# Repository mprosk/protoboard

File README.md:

# protoboard
General purpose prototyping breadboard

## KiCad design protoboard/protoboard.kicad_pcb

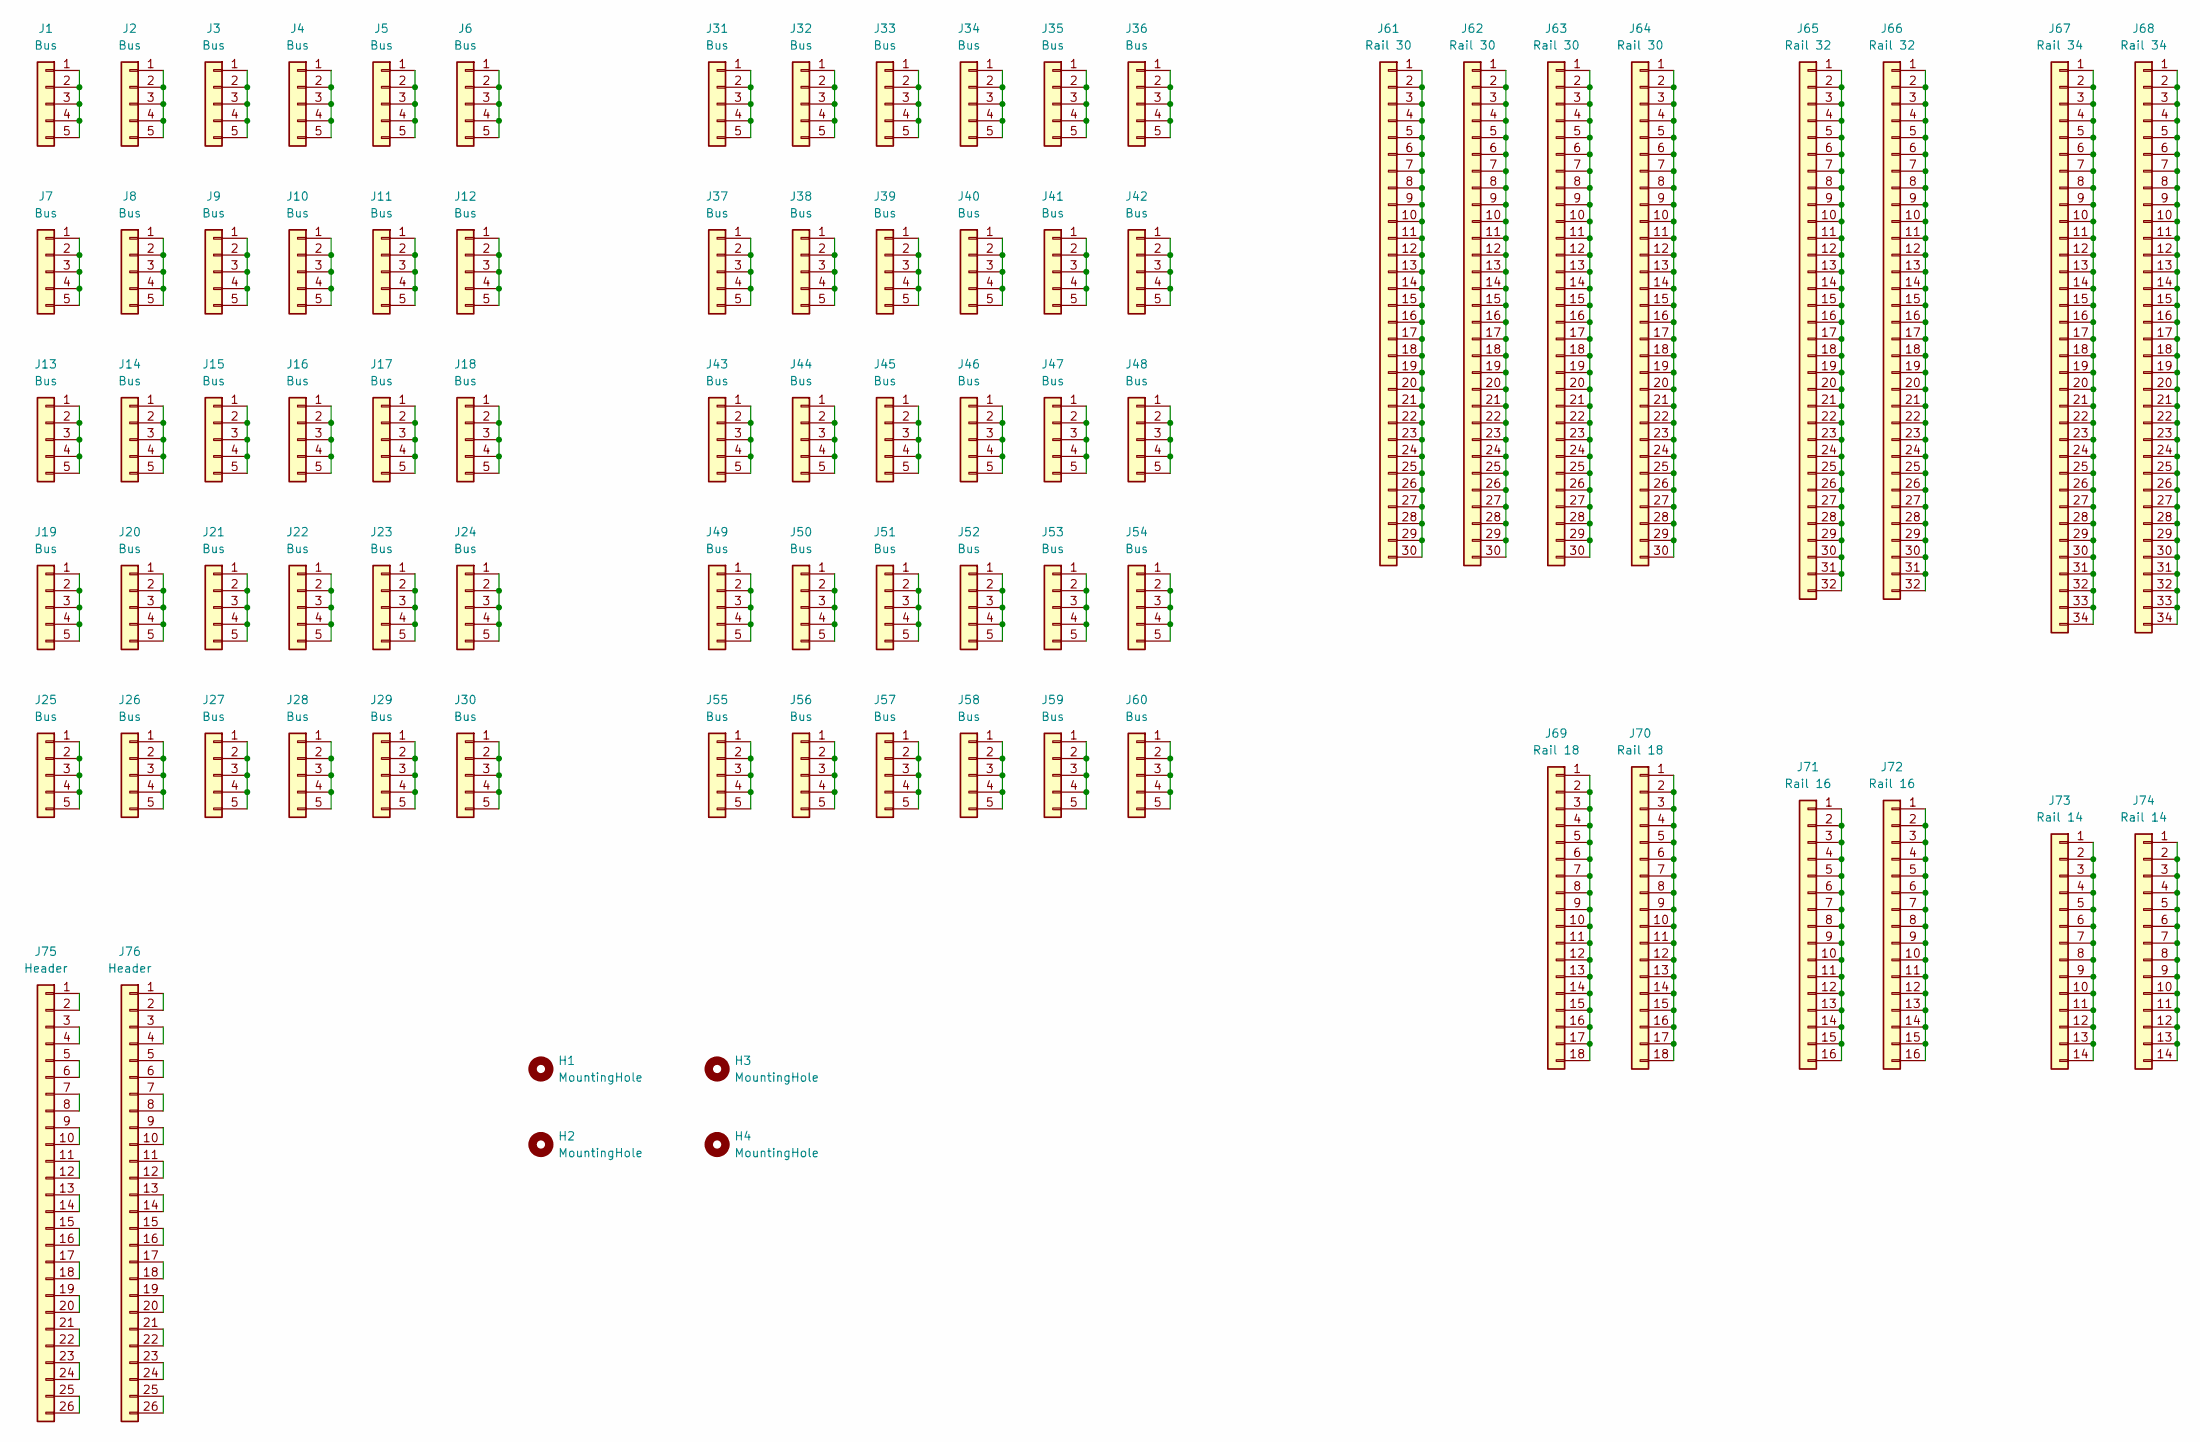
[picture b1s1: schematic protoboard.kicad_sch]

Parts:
H1, H2, H3, H4: MountingHole; MountingHole_3.2mm_M3
J1, J2, J3, J4, J5, J6, J7, J8, J9, J10, J11, J12, J13, J14, J15, J16, J17, J18, J19, J20, J21, J22, J23, J24, J25, J26, J27, J28, J29, J30, J31, J32, J33, J34, J35, J36, J37, J38, J39, J40, J41, J42, J43, J44, J45, J46, J47, J48, J49, J50, J51, J52, J53, J54, J55, J56, J57, J58, J59, J60: Bus
J61, J62, J63, J64: Rail 30; Rail_30
J65, J66: Rail 32; Rail_32
J67, J68: Rail 34; Rail_34
J69, J70: Rail 18; Rail_18
J71, J72: Rail 16; Rail_16
J73, J74: Rail 14; Rail_14
J75, J76: Header

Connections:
unnamed: J1.1, J1.2, J1.3, J1.4, J1.5
unnamed: J2.1, J2.2, J2.3, J2.4, J2.5
unnamed: J3.1, J3.2, J3.3, J3.4, J3.5
unnamed: J4.1, J4.2, J4.3, J4.4, J4.5
unnamed: J5.1, J5.2, J5.3, J5.4, J5.5
unnamed: J6.1, J6.2, J6.3, J6.4, J6.5
unnamed: J7.1, J7.2, J7.3, J7.4, J7.5
unnamed: J8.1, J8.2, J8.3, J8.4, J8.5
unnamed: J9.1, J9.2, J9.3, J9.4, J9.5
unnamed: J10.1, J10.2, J10.3, J10.4, J10.5
unnamed: J11.1, J11.2, J11.3, J11.4, J11.5
unnamed: J12.1, J12.2, J12.3, J12.4, J12.5
unnamed: J13.1, J13.2, J13.3, J13.4, J13.5
unnamed: J14.1, J14.2, J14.3, J14.4, J14.5
unnamed: J15.1, J15.2, J15.3, J15.4, J15.5
unnamed: J16.1, J16.2, J16.3, J16.4, J16.5
unnamed: J17.1, J17.2, J17.3, J17.4, J17.5
unnamed: J18.1, J18.2, J18.3, J18.4, J18.5
unnamed: J19.1, J19.2, J19.3, J19.4, J19.5
unnamed: J20.1, J20.2, J20.3, J20.4, J20.5
unnamed: J21.1, J21.2, J21.3, J21.4, J21.5
unnamed: J22.1, J22.2, J22.3, J22.4, J22.5
unnamed: J23.1, J23.2, J23.3, J23.4, J23.5
unnamed: J24.1, J24.2, J24.3, J24.4, J24.5
unnamed: J25.1, J25.2, J25.3, J25.4, J25.5
unnamed: J26.1, J26.2, J26.3, J26.4, J26.5
unnamed: J27.1, J27.2, J27.3, J27.4, J27.5
unnamed: J28.1, J28.2, J28.3, J28.4, J28.5
unnamed: J29.1, J29.2, J29.3, J29.4, J29.5
unnamed: J30.1, J30.2, J30.3, J30.4, J30.5
unnamed: J31.1, J31.2, J31.3, J31.4, J31.5
unnamed: J32.1, J32.2, J32.3, J32.4, J32.5
unnamed: J33.1, J33.2, J33.3, J33.4, J33.5
unnamed: J34.1, J34.2, J34.3, J34.4, J34.5
unnamed: J35.1, J35.2, J35.3, J35.4, J35.5
unnamed: J36.1, J36.2, J36.3, J36.4, J36.5
unnamed: J37.1, J37.2, J37.3, J37.4, J37.5
unnamed: J38.1, J38.2, J38.3, J38.4, J38.5
unnamed: J39.1, J39.2, J39.3, J39.4, J39.5
unnamed: J40.1, J40.2, J40.3, J40.4, J40.5
unnamed: J41.1, J41.2, J41.3, J41.4, J41.5
unnamed: J42.1, J42.2, J42.3, J42.4, J42.5
unnamed: J43.1, J43.2, J43.3, J43.4, J43.5
unnamed: J44.1, J44.2, J44.3, J44.4, J44.5
unnamed: J45.1, J45.2, J45.3, J45.4, J45.5
unnamed: J46.1, J46.2, J46.3, J46.4, J46.5
unnamed: J47.1, J47.2, J47.3, J47.4, J47.5
unnamed: J48.1, J48.2, J48.3, J48.4, J48.5
unnamed: J49.1, J49.2, J49.3, J49.4, J49.5
unnamed: J50.1, J50.2, J50.3, J50.4, J50.5
unnamed: J51.1, J51.2, J51.3, J51.4, J51.5
unnamed: J52.1, J52.2, J52.3, J52.4, J52.5
unnamed: J53.1, J53.2, J53.3, J53.4, J53.5
unnamed: J54.1, J54.2, J54.3, J54.4, J54.5
unnamed: J55.1, J55.2, J55.3, J55.4, J55.5
unnamed: J56.1, J56.2, J56.3, J56.4, J56.5
unnamed: J57.1, J57.2, J57.3, J57.4, J57.5
unnamed: J58.1, J58.2, J58.3, J58.4, J58.5
unnamed: J59.1, J59.2, J59.3, J59.4, J59.5
unnamed: J60.1, J60.2, J60.3, J60.4, J60.5
unnamed: J61.1, J61.2, J61.3, J61.4, J61.5, J61.6, J61.7, J61.8, J61.9, J61.10, J61.11, J61.12, J61.13, J61.14, J61.15, J61.16, J61.17, J61.18, J61.19, J61.20, J61.21, J61.22, J61.23, J61.24, J61.25, J61.26, J61.27, J61.28, J61.29, J61.30
unnamed: J62.1, J62.2, J62.3, J62.4, J62.5, J62.6, J62.7, J62.8, J62.9, J62.10, J62.11, J62.12, J62.13, J62.14, J62.15, J62.16, J62.17, J62.18, J62.19, J62.20, J62.21, J62.22, J62.23, J62.24, J62.25, J62.26, J62.27, J62.28, J62.29, J62.30
unnamed: J63.1, J63.2, J63.3, J63.4, J63.5, J63.6, J63.7, J63.8, J63.9, J63.10, J63.11, J63.12, J63.13, J63.14, J63.15, J63.16, J63.17, J63.18, J63.19, J63.20, J63.21, J63.22, J63.23, J63.24, J63.25, J63.26, J63.27, J63.28, J63.29, J63.30
unnamed: J64.1, J64.2, J64.3, J64.4, J64.5, J64.6, J64.7, J64.8, J64.9, J64.10, J64.11, J64.12, J64.13, J64.14, J64.15, J64.16, J64.17, J64.18, J64.19, J64.20, J64.21, J64.22, J64.23, J64.24, J64.25, J64.26, J64.27, J64.28, J64.29, J64.30
unnamed: J65.1, J65.2, J65.3, J65.4, J65.5, J65.6, J65.7, J65.8, J65.9, J65.10, J65.11, J65.12, J65.13, J65.14, J65.15, J65.16, J65.17, J65.18, J65.19, J65.20, J65.21, J65.22, J65.23, J65.24, J65.25, J65.26, J65.27, J65.28, J65.29, J65.30, J65.31, J65.32
unnamed: J66.1, J66.2, J66.3, J66.4, J66.5, J66.6, J66.7, J66.8, J66.9, J66.10, J66.11, J66.12, J66.13, J66.14, J66.15, J66.16, J66.17, J66.18, J66.19, J66.20, J66.21, J66.22, J66.23, J66.24, J66.25, J66.26, J66.27, J66.28, J66.29, J66.30, J66.31, J66.32
unnamed: J67.1, J67.2, J67.3, J67.4, J67.5, J67.6, J67.7, J67.8, J67.9, J67.10, J67.11, J67.12, J67.13, J67.14, J67.15, J67.16, J67.17, J67.18, J67.19, J67.20, J67.21, J67.22, J67.23, J67.24, J67.25, J67.26, J67.27, J67.28, J67.29, J67.30, J67.31, J67.32, J67.33, J67.34
unnamed: J68.1, J68.2, J68.3, J68.4, J68.5, J68.6, J68.7, J68.8, J68.9, J68.10, J68.11, J68.12, J68.13, J68.14, J68.15, J68.16, J68.17, J68.18, J68.19, J68.20, J68.21, J68.22, J68.23, J68.24, J68.25, J68.26, J68.27, J68.28, J68.29, J68.30, J68.31, J68.32, J68.33, J68.34
unnamed: J69.1, J69.2, J69.3, J69.4, J69.5, J69.6, J69.7, J69.8, J69.9, J69.10, J69.11, J69.12, J69.13, J69.14, J69.15, J69.16, J69.17, J69.18
unnamed: J70.1, J70.2, J70.3, J70.4, J70.5, J70.6, J70.7, J70.8, J70.9, J70.10, J70.11, J70.12, J70.13, J70.14, J70.15, J70.16, J70.17, J70.18
unnamed: J71.1, J71.2, J71.3, J71.4, J71.5, J71.6, J71.7, J71.8, J71.9, J71.10, J71.11, J71.12, J71.13, J71.14, J71.15, J71.16
unnamed: J72.1, J72.2, J72.3, J72.4, J72.5, J72.6, J72.7, J72.8, J72.9, J72.10, J72.11, J72.12, J72.13, J72.14, J72.15, J72.16
unnamed: J73.1, J73.2, J73.3, J73.4, J73.5, J73.6, J73.7, J73.8, J73.9, J73.10, J73.11, J73.12, J73.13, J73.14
unnamed: J74.1, J74.2, J74.3, J74.4, J74.5, J74.6, J74.7, J74.8, J74.9, J74.10, J74.11, J74.12, J74.13, J74.14
unnamed: J75.1, J75.2
unnamed: J75.3, J75.4
unnamed: J75.5, J75.6
unnamed: J75.7, J75.8
unnamed: J75.9, J75.10
unnamed: J75.11, J75.12
unnamed: J75.13, J75.14
unnamed: J75.15, J75.16
unnamed: J75.17, J75.18
unnamed: J75.19, J75.20
unnamed: J75.21, J75.22
unnamed: J75.23, J75.24
unnamed: J75.25, J75.26
unnamed: J76.1, J76.2
unnamed: J76.3, J76.4
unnamed: J76.5, J76.6
unnamed: J76.7, J76.8
unnamed: J76.9, J76.10
unnamed: J76.11, J76.12
unnamed: J76.13, J76.14
unnamed: J76.15, J76.16
unnamed: J76.17, J76.18
unnamed: J76.19, J76.20
unnamed: J76.21, J76.22
unnamed: J76.23, J76.24
unnamed: J76.25, J76.26

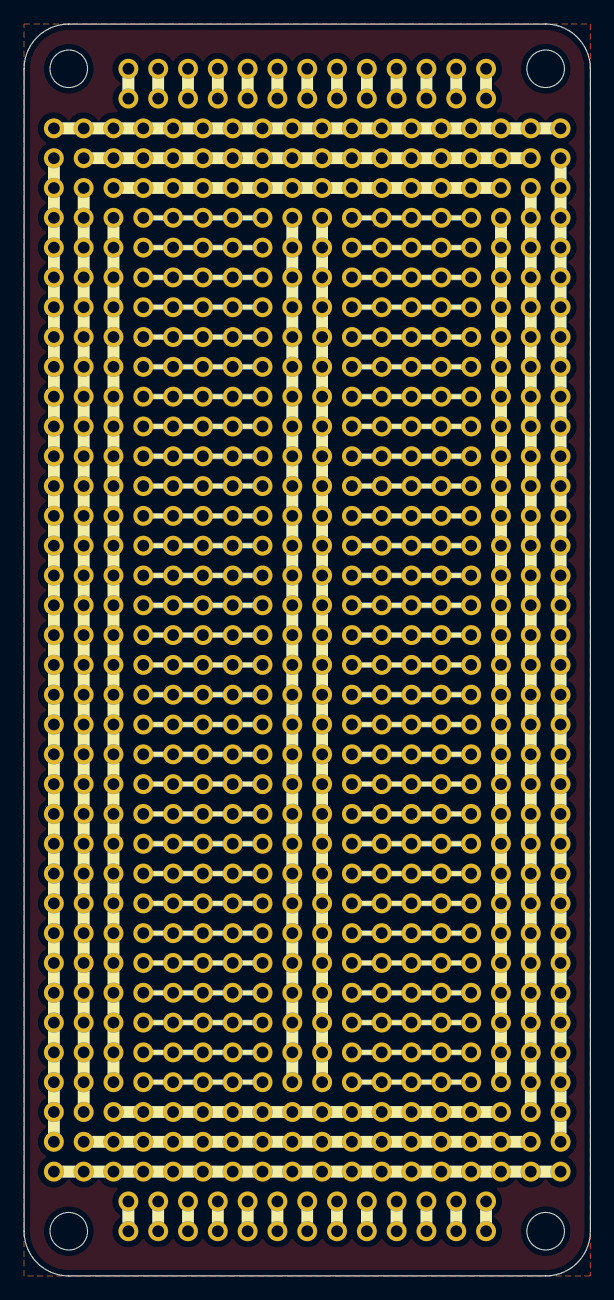
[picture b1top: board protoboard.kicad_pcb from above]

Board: 2 copper layers, 48.3 x 106.7 mm, 80 parts (0 on the bottom side), 100 nets.

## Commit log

2022-09-13 Copy files from local
2022-09-13 Export gerbers
2022-09-19 Fix silkscreen
